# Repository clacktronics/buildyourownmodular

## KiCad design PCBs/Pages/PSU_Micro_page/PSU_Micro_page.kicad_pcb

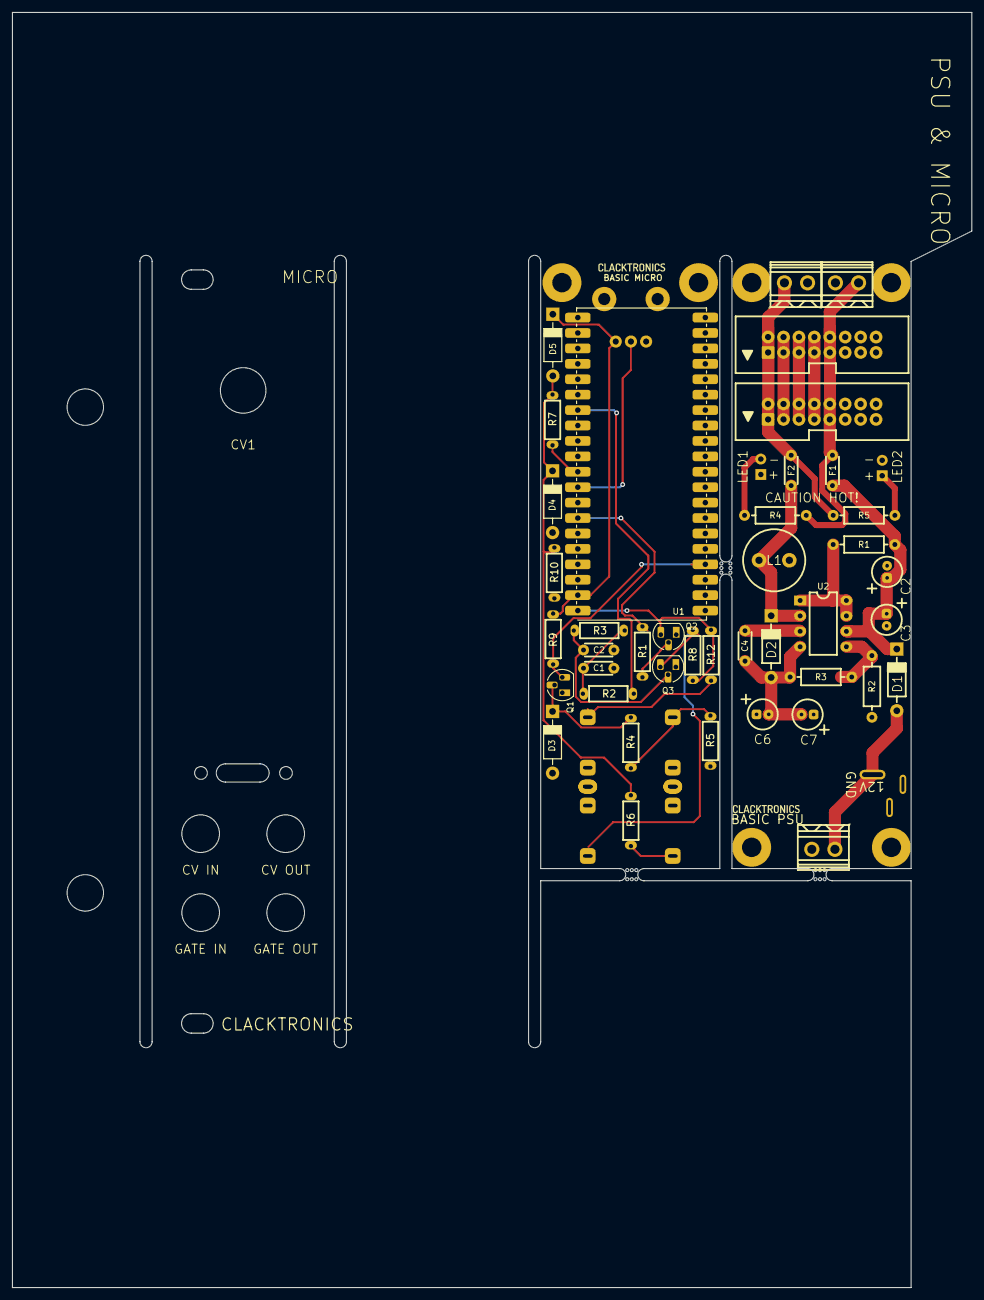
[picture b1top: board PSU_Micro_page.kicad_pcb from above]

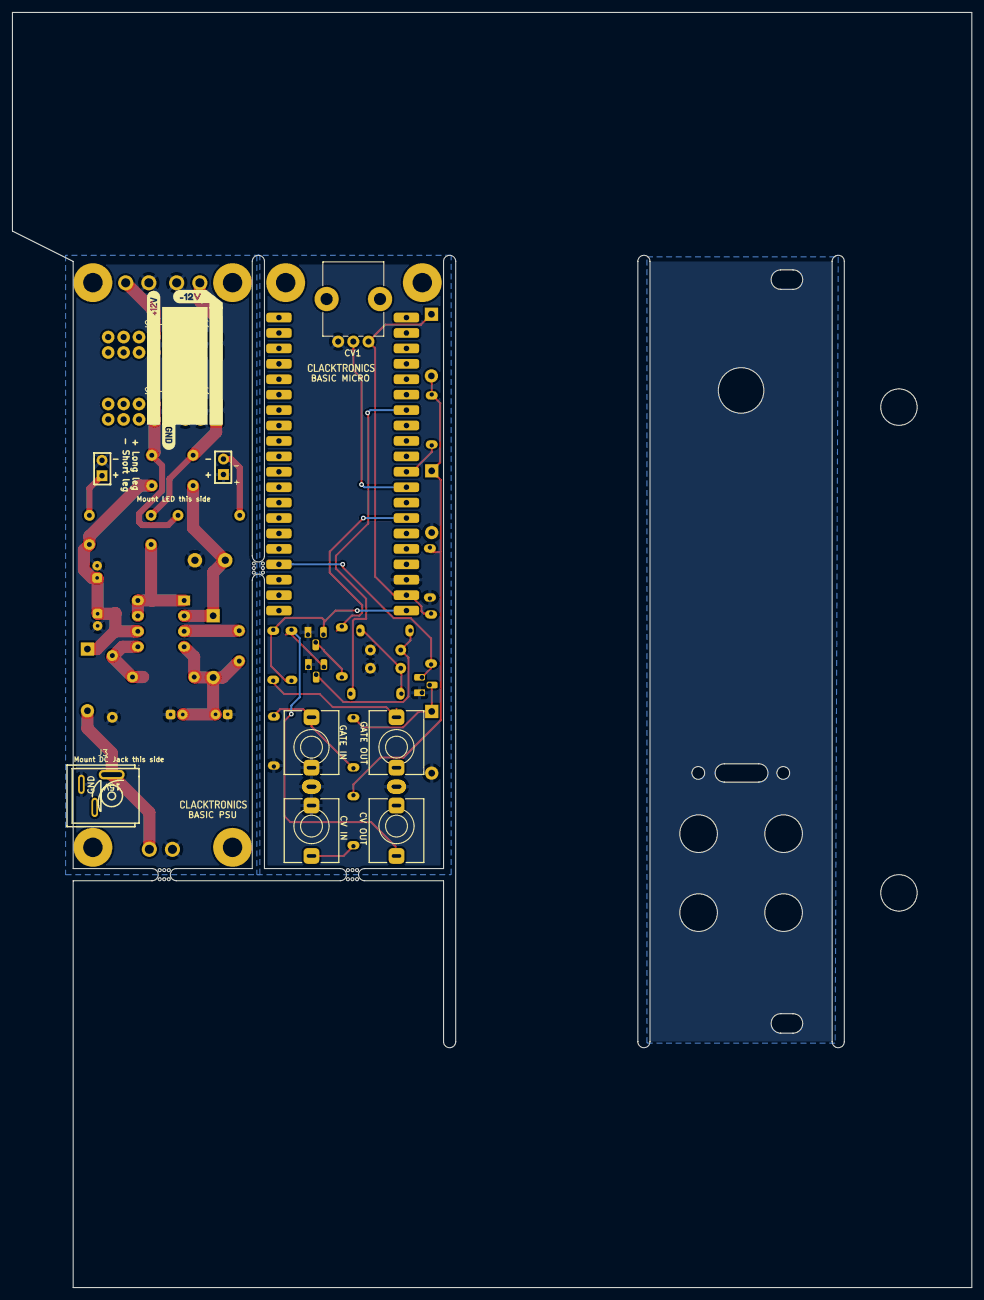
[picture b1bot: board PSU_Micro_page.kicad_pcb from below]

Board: 2 copper layers, 158.0 x 210.0 mm, 55 parts (9 on the bottom side), 28 nets.

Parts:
C1, C2#2: C; C_TH_Disc_P5.00mm
C2, C3, C6, C7: 100μF; C_TH_Elec_5mm_P2mm
C4: 220pF; C_TH_Disc_P5.00mm
D1, D2: 1N5819; D_TH_DO-41_P10.16mm
D3, D4, D5: 1N5819WS; D_TH_DO-41_P10.16mm
F1, F2: JK60-030; C_TH_Disc_P5.00mm
J1, J4, J21: Screw_Terminal_01x02; CONN-TH_2P-P3.81_DB125-3.81-2P-BK-S
J2, J17: EURORACK_16_PIN; Eurorack-IDC-Header
J2#2: GATE_OUT; Jack_3.5mm_QingPu_WQP-PJ398SM_Vertical
J3: 12V input; DC-IN-TH_DC-012A-20A
J4#2: CV_IN; Jack_3.5mm_QingPu_WQP-PJ398SM_Vertical
J5: CV_OUT; Jack_3.5mm_QingPu_WQP-PJ398SM_Vertical
J7: GATE_IN; Jack_3.5mm_QingPu_WQP-PJ398SM_Vertical
L1: 220μH; L_Radial_D10.0mm_P5.00mm_Neosid_SD12_style3
LED1, LED2: LED; LED_D3.0mm
Q1, Q2, Q3: 2N3904; TO-92_HandSolder
R1, R2#2, R3#2, R7, R8, R9, R12: 1k; R_Axial_DIN0204_L3.6mm_D1.6mm_P7.62mm_Horizontal
R1#2: 1Ω; R_TH_Axial_250mw_P10.16mm_Horizontal
R2: 13kΩ; R_TH_Axial_250mw_P10.16mm_Horizontal
R3, R4#2, R5#2: 1.5kΩ; R_TH_Axial_250mw_P10.16mm_Horizontal
R4, R5, R10: 100k; R_Axial_DIN0204_L3.6mm_D1.6mm_P7.62mm_Horizontal
R6: 220k; R_Axial_DIN0204_L3.6mm_D1.6mm_P7.62mm_Horizontal
RV1: 10k; POT_TH_Alps_RK09K_Single_Vertical
U1: Raspberry_Pi_Pico; RPI_Pico_through_hole
U2: MC34063AD; DIP-8_W7.62mm_LongPads
kibuzzard-63C1369E: G***; kibuzzard-63C1369E
kibuzzard-63C13629: G***; kibuzzard-63C13629
kibuzzard-6399AAFB: G***; kibuzzard-6399AAFB
mouse-bite-2mm-slot, mouse-bite-2mm-slot#2, mouse-bite-2mm-slot#3: VAL**; mouse-bite-2mm-slot

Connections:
+3.3V: D5.1 (K), R9.1, RV1.1, U1.39 (VSYS)
+5V: Q2.3 (C), R8.1, R12.2, U1.40 (VBUS)
+12V: F1.2, J2.9, J2.10, J4.2, J17.9, J17.10, R4#2.2
-12V: F2.2, J2.1, J2.2, J17.1, J17.2, J21.1, R5#2.2
GND: C1.2, C2.2, C2#2.2, C3.2, C6.1, C7.1, D3.2 (A), D4.2 (A), J1.2, J2.3, J2.4, J2.5, J2.6, J2.7, J2.8, J2#2.S, J3.2, J4.1, J4#2.S, J4#2.TN, J5.S, J7.S, J7.TN, J17.3, J17.4, J17.5, J17.6, J17.7, J17.8, J21.2, L1.2, LED1.1 (K), LED2.2 (A), Q1.1 (E), Q2.1 (E), Q3.1 (E), R2.1, R5.1, R10.1, RV1.3, U1.38 (GND)
unnamed: C1.1, R2#2.1, R3#2.2
unnamed: D1.2 (A), J1.1, J3.1
unnamed: C4.2, C6.2, C7.2, D2.2 (A), R3.1, U2.4 (GND)
unnamed: D2.1 (K), F2.1, L1.1, U2.2 (SwE)
unnamed: D3.1 (K), Q1.2 (B), R4.2
unnamed: D4.1 (K), D5.2 (A), R6.2, R7.2, R10.2
unnamed: J2#2.T, R12.1
unnamed: J4#2.T, R6.1
unnamed: J7.T, R4.1, R5.2
unnamed: LED1.2 (A), R4#2.1
unnamed: LED2.1 (K), R5#2.1
unnamed: Q1.3 (C), R9.2, U1.4 (GP2)
unnamed: Q2.2 (B), R1.1
unnamed: C2#2.1, Q3.2 (B), R3#2.1
unnamed: J5.T, Q3.3 (C), R8.2
unnamed: R2#2.2, U1.27 (GP21)
unnamed: R7.1, U1.31 (GP26)
unnamed: RV1.2, U1.32 (GP27)
unnamed: R1.2, U1.34 (GP28)
unnamed: R1#2.2, U2.1 (SwC), U2.7 (Ipk), U2.8 (DC)
unnamed: C4.1, U2.3 (TC)
unnamed: R2.2, R3.2, U2.5 (Vfb)
VCC: C2.1, C3.1, D1.1 (K), F1.1, R1#2.1, U2.6 (Vin)

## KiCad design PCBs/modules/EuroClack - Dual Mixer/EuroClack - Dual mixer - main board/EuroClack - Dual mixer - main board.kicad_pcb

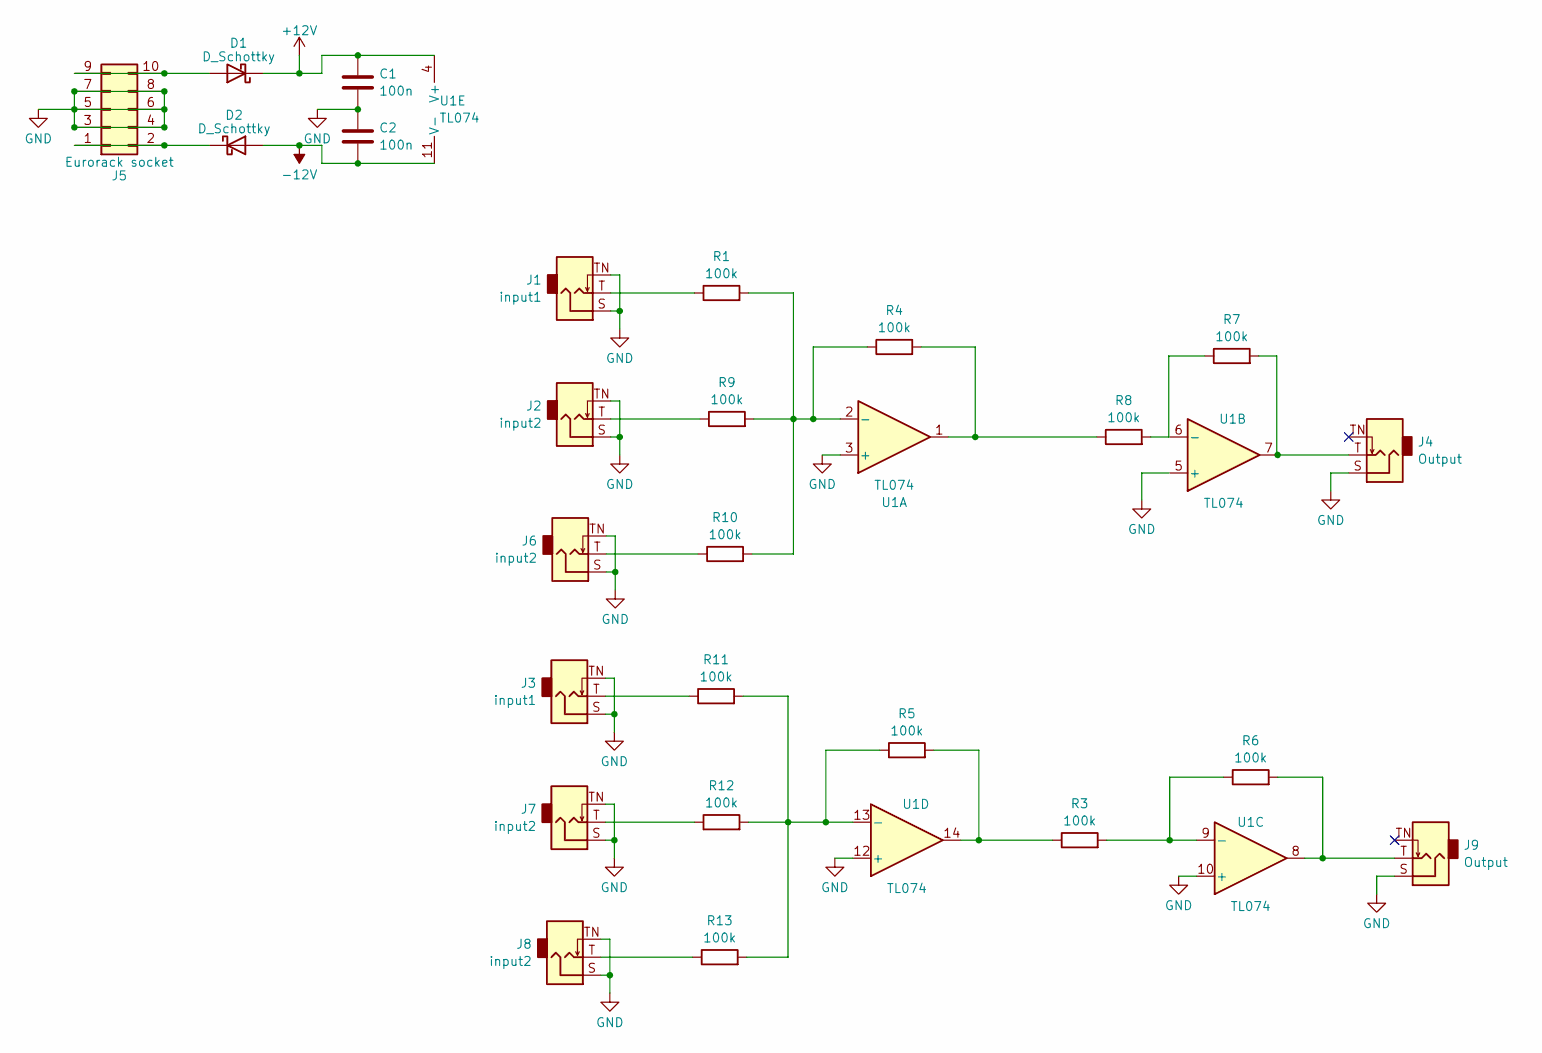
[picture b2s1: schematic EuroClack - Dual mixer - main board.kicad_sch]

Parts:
C1, C2: 100n; C_TH_Disc_P5.00mm
D1, D2: D_Schottky; D_TH_DO-41_P10.16mm
J1, J3: input1; Jack_3.5mm_QingPu_WQP-PJ366ST_Vertical
J2, J6, J7, J8: input2; Jack_3.5mm_QingPu_WQP-PJ366ST_Vertical
J4, J9: Output; Jack_3.5mm_QingPu_WQP-PJ366ST_Vertical
J5: Eurorack socket; IDC-Header_2x05_P2.54mm_Vertical
R1, R3, R4, R5, R6, R7, R8, R9, R10, R11, R12, R13: 100k; R_Axial_DIN0204_L3.6mm_D1.6mm_P7.62mm_Horizontal
U1: TL074; DIP-14_W7.62mm_LongPads

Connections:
+12V: C1.1, D1.1 (K), U1.4 (V+)
-12V: C2.2, D2.2 (A), U1.11 (V-)
GND: C1.2, C2.1, J1.S, J1.TN, J2.S, J2.TN, J3.S, J3.TN, J4.S, J5.3, J5.4, J5.5, J5.6, J5.7, J5.8, J6.S, J6.TN, J7.S, J7.TN, J8.S, J8.TN, J9.S, U1.3 (+), U1.10 (+), U1.12 (+)
unnamed: D1.2 (A), J5.9, J5.10
unnamed: D2.1 (K), J5.1, J5.2
unnamed: J1.T, R1.1
unnamed: J2.T, R9.1
unnamed: J3.T, R11.1
unnamed: J4.T, R7.2, U1.7
unnamed: J6.T, R10.1
unnamed: J7.T, R12.1
unnamed: J8.T, R13.1
unnamed: J9.T, R6.2, U1.8
unnamed: R1.2, R9.2, R10.2
unnamed: R3.1, R5.2, U1.14
unnamed: R4.2, R8.1, U1.1
unnamed: R7.1, R8.2
unnamed: R11.2, R12.2, R13.2
unnamed: R4.1, U1.2 (-)
unnamed: R3.2, R6.1, U1.9 (-)
unnamed: R5.1, U1.13 (-)

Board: 2 copper layers, 26 parts (3 on the bottom side), 21 nets, no tracks yet.
